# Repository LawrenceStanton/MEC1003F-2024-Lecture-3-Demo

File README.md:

# MEC1003F Lecture 3 Demo

KiCad Demonstration Project for UCT MEC1003F 2024.

## Lesson Plan

In this lecture we will continue from the previous project's schematic. In the last lecture we made some footprints and assigned them to the schematic components. In the assignment we also added a voltage regulator to the same circuit. Either project can continue to be used for this lecture, but this project will be used as the reference.

The lecture will also contain a fair bit of information on the PCB manufacturing process, which is not detailed in this project.

## Overview

This project retains the original project structure as previously used. The main project [MEC1003F 2024 Lecture 3 Demo.kicad_pro](MEC1003F%202024%20Lecture%203%20Demo.kicad_pro) contains:

- A single Schematic file [MEC1003F 2024 Lecture 3 Demo.kicad_sch](MEC1003F%202024%20Lecture%203%20Demo.kicad_sch).
- A single PCB file [MEC1003F 2024 Lecture 3 Demo.kicad_pcb](MEC1003F%202024%20Lecture%203%20Demo.kicad_pcb).
- A project symbols library [Project Symbols.kicad_sym](Project%20Symbols.kicad_sym).
- A project footprints library [Project Footprints.pretty](Project%20Footprints.pretty).

Today we are going to focus on the PCB file.

## PCB Information

Before we start laying out routing the PCB, we must learn a bit about how PCBs are made in order to understand the limitations our design must adhere to. The first bif of the lecture will cover this.

## PCB Layout & Routing

Now that we are familiar with the PCB manufacturing process, we can start doing something! Today we will over the following tasks:

### Task 1: Design Rules

Before we start routing, we need to set up the design rules. This is done in the `Design Rules` section under the `File > Board Setup` menu. The design rules are the constraints that the PCB layout must adhere to in order to be manufacturable. The design rules are set by the manufacturer and are usually available on their website. We must translate these rules into KiCad's design rules.

For this lecture we will follow the design rules of [JLCPCB](https://jlcpcb.com/). The design rules are available at [https://jlcpcb.com/capabilities/Capabilities](https://jlcpcb.com/capabilities/Capabilities).

In the lecture I will walk the class through this. It is not a 1:1 translation! The manufacturer capabilities are the absolute limit, and it is good engineering practice to give some margin on these specs. For example, the minimum trace width is 0.127mm, but we will use 0.30mm. You must use your judgement based on the design requirements, the manufacturer's capabilities, and the sensitivity of these specifications when setting the design rules.

### Task 2: Board Outline

The board outline is the physical boundary of the PCB. In KiCad the board outline is set in the `Edge.Cuts` layer with a simple closed path using the drawing tools. For this demo there is no requirements for a complex shape, and for the amount of components we have, a simple 30x30mm square will suffice.

Place a board outline by using the rectangle drawing tool in the `Edge.Cuts` layer.

### Task 3: Component Placement

In the demo project I did some component placement already for half the circuit. It is hard to really teach component placement, it's very much subjective and there's a degree of style to it, especially when there are no electromagnetic or thermal requirements. But there are some general guidelines:

- Set as high a grid scale as possible for the components you are placing. This makes it easier to align and stop worrying about exact locations.
- Hide the silkscreen and other unnecessary layers. Those are secondary concerns to be dealt with later.
- Place the things which must be at a particular location first. This mostly means connectors and mechanical mounting holes. Easy enough. As for the rest...
- Orient passive components around the central component (usually some integrated circuit) that they are supporting. This brings a logical grouping to the components, like how the schematic would have been drawn. Do this to the side in free space - do not consider the rest of the board yet. Just focus on this group of components fitting well with each other. Repeat for each group of components.
- Place passive components in rows along the face of the IC. It looks right and simplifies things. Don't try overcomplicating the layout - there is likely to be zero functional benefit.
- Don't route the components yet. Just place them, or only route obvious and short connections. It becomes harder to move components once they are routed. The rats nest lines will rather show you if the routing will be simple with the layout until you're ready to go.
- Use vias sparingly, but use them. They don't add any cost, the main impact is the space they take up. At a certain point that space is worth it though over long meandering traces.
- All power and ground nets, just route to a quick via. Drop it to the bottom later and move on. GND will connect to a ground plane and power we'll deal with later.
- A good rule of thumb is to set a trace with that us 60-80% of the pad width you're starting from. It looks good, and if the trace needed to be thicker then probably the pad would be bigger too. Only increase the trace width along the track length if you have a reason, like if it is a long trace.
- Polygons can be used for power planes, but while we only have a 2 layer board without any high power components we can simply route power like any other trace. You can use power plane polygons when you have more layers and more complex power delivery requirements.
- Once a subcircuit is laid out and routed, move that group can be considered a unit and placed on the board space accordingly. With a bigger shape it will be more obvious to see which orientation and location is best.

It is a long process and the only way to do it quickly is with some practise. For this assignment, simply layout, route, delete and repeat until you are happy with your speed and the result.

### Task 4: Gerber Files

The final task in this lecture is to generate the Gerber files. These are the files that the PCB manufacturer will use to make the PCB.

## Next Lecture

That is the end of this course's core content! You should now know how to make a simple PCB from start to finish. The next lecture is dedicated to preparation for the class test, where I will demonstrate what you will be asked to do under test conditions.

I'll do this test demo in less than the allocated time, so I'll also show you some of the things I skipped over earlier, like the Electric Rules Checker and multipart symbols, which are good to know but not essential for the test. I'll also show what is needed for automatic assembly for JLCPCB, which requires some extra information to be added to the Bill of Materials and Pick n Place files.

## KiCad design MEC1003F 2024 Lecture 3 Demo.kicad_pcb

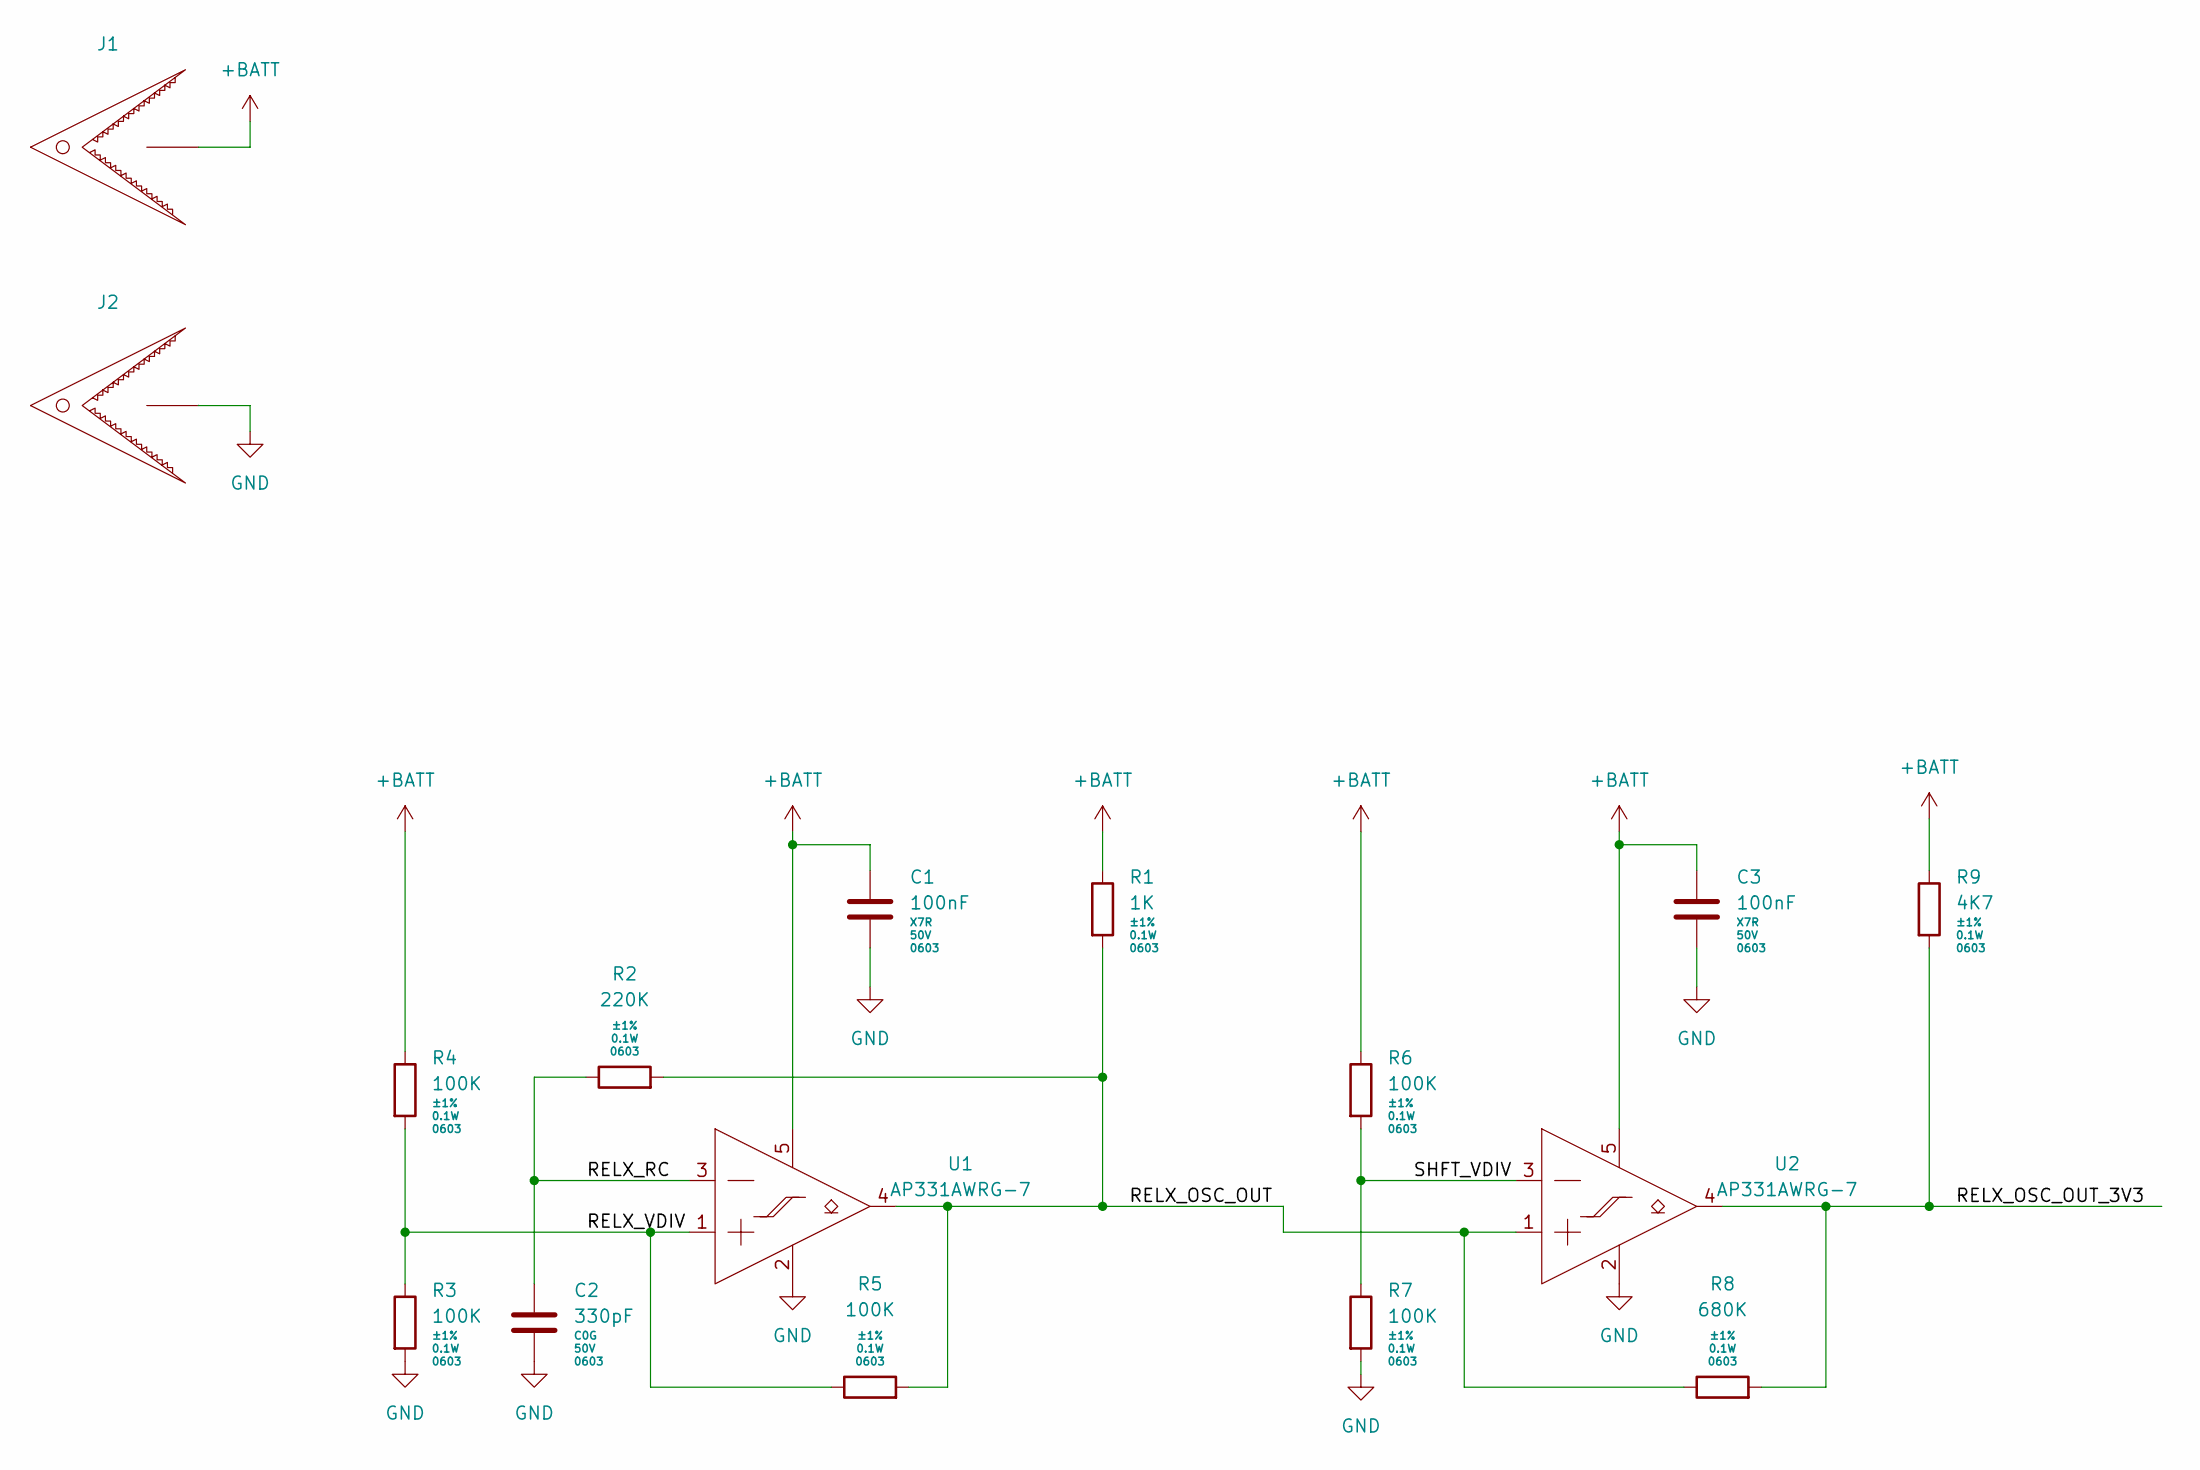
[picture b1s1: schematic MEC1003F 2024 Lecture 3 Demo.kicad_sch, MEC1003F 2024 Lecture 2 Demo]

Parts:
C1, C3: 100nF; C_0603_1608Metric; Voltage 50V
C2: 330pF; C_0603_1608Metric; Voltage 50V
J1, J2: CROC
R1: 1K; R_0603_1608Metric; Tolerance ±1%
R2: 220K; R_0603_1608Metric; Tolerance ±1%
R3, R4, R5, R6, R7: 100K; R_0603_1608Metric; Tolerance ±1%
R8: 680K; R_0603_1608Metric; Tolerance ±1%
R9: 4K7; R_0603_1608Metric; Tolerance ±1%
U1, U2: AP331AWRG-7; SOT-23-5 (AP331A)

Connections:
+BATT: C1.1, C3.1, J1.1, R1.1, R4.1, R6.1, R9.1, U1.5 (VCC), U2.5 (VCC)
/RELX_OSC_OUT: R1.2, R2.2, R5.2, R8.1, U1.4 (OUT), U2.1 (IN+)
/RELX_OSC_OUT_3V3: R8.2, R9.2, U2.4 (OUT)
/RELX_RC: C2.1, R2.1, U1.3 (IN-)
/RELX_VDIV: R3.1, R4.2, R5.1, U1.1 (IN+)
/SHFT_VDIV: R6.2, R7.1, U2.3 (IN-)
GND: C1.2, C2.2, C3.2, J2.1, R3.2, R7.2, U1.2 (GND), U2.2 (GND)

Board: 2 copper layers, 16 parts (0 on the bottom side), 7 nets, no tracks yet.

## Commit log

2024-04-18 Apply Lecture 2 Changes Rename Project Update README.md

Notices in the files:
MEC1003F 2024 Lecture 3 Demo.kicad_sch:
Licence: Creative Commons
